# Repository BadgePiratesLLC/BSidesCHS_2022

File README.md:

# BSidesCHS_2022
BSides Charleston 2022

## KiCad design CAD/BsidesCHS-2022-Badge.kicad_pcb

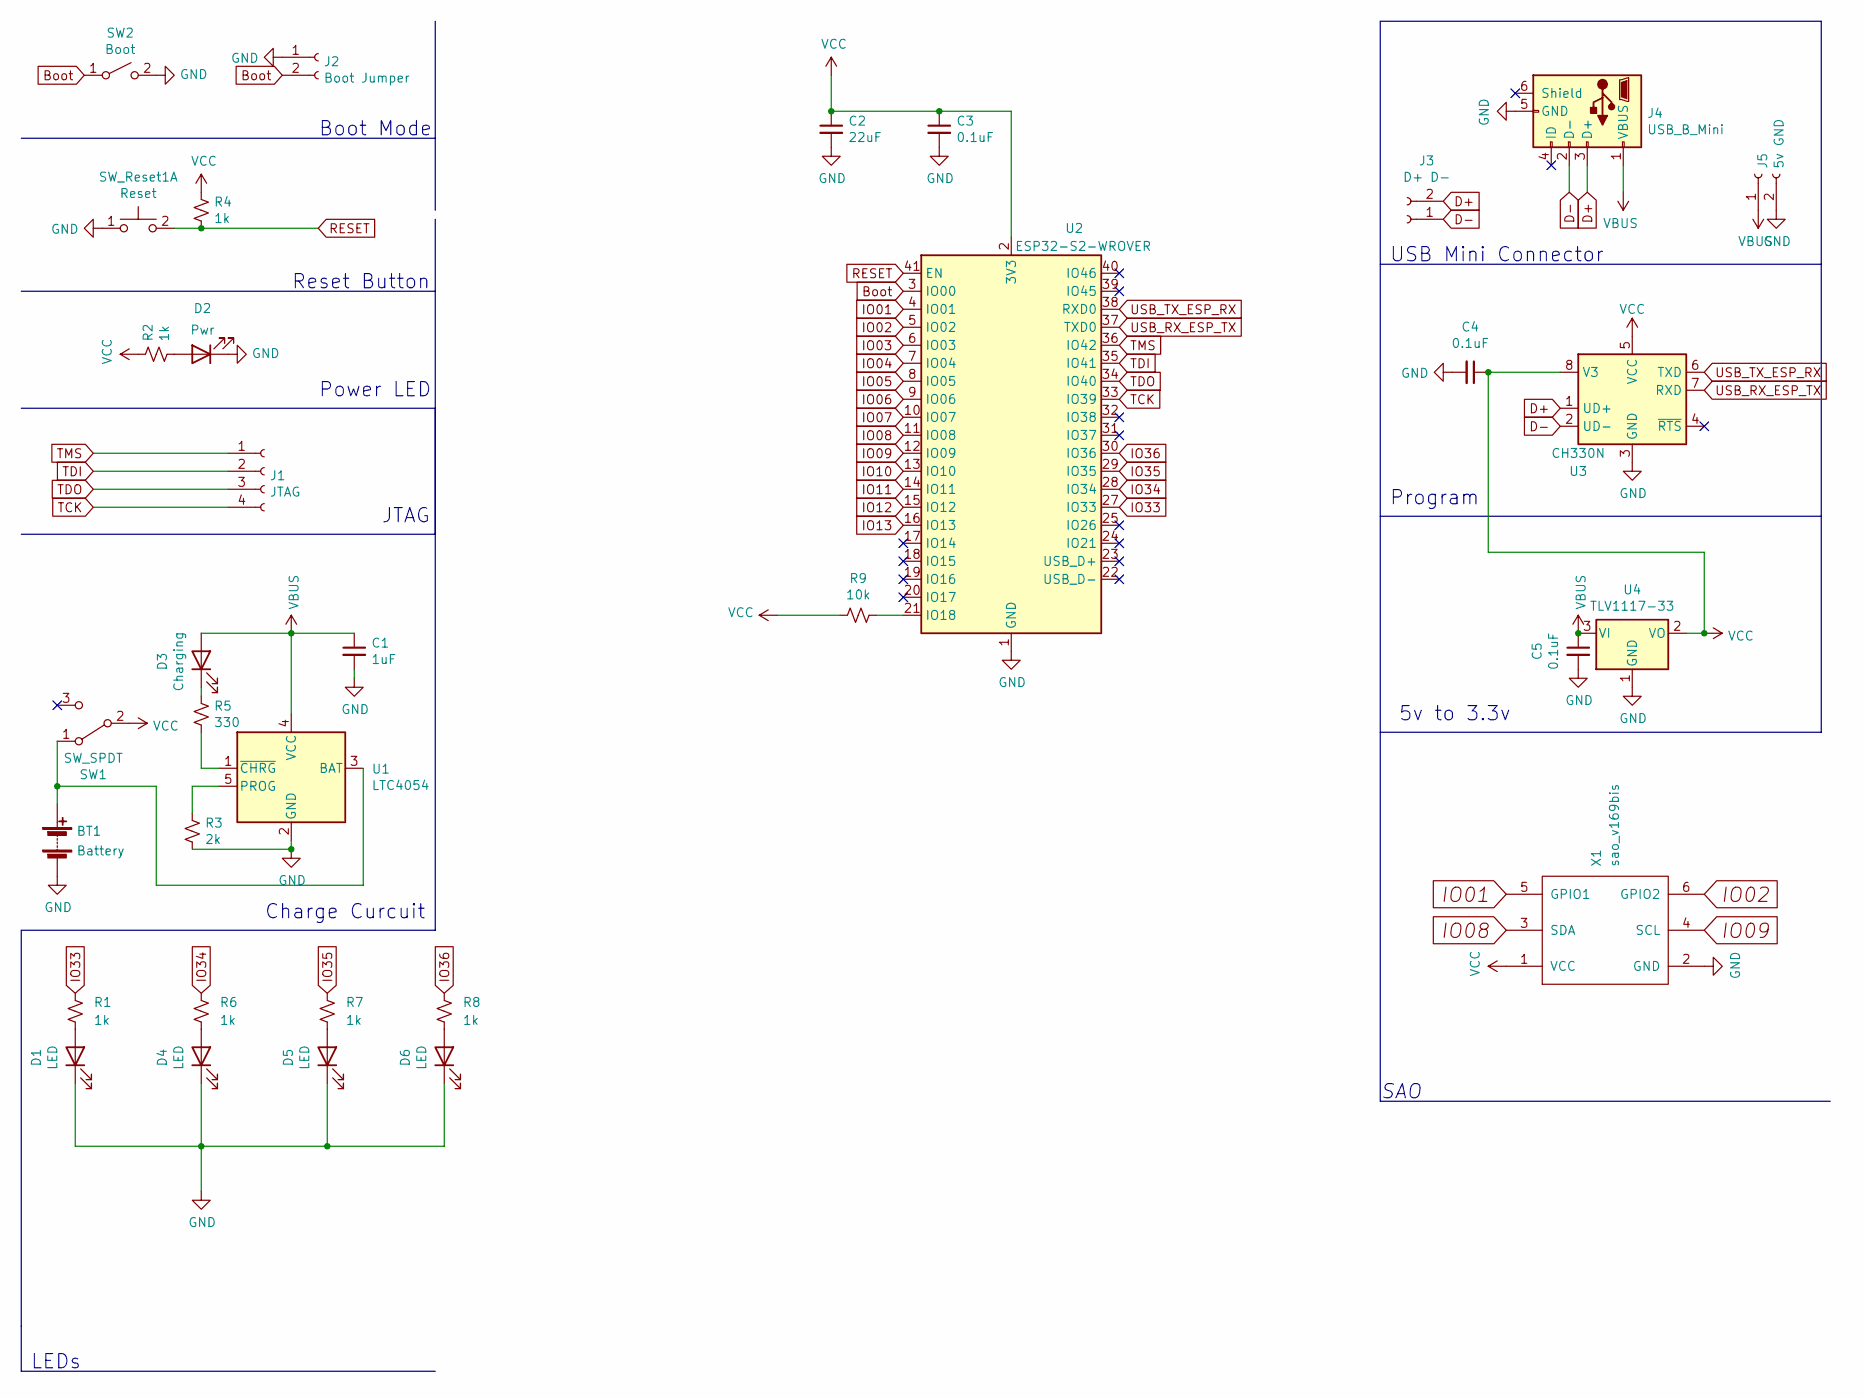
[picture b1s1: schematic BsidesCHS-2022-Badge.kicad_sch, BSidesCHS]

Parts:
BT1: Battery; Battery - 14500
C1: 1uF; C_0805_2012Metric
C2: 22uF; C_0805_2012Metric
C3, C4, C5: 0.1uF; C_0805_2012Metric
D1, D4, D5, D6: LED; LED_Osram_Lx_P47F_D2mm_ReverseMount_Proper_Mask Only
D2: Pwr; R_1206_3216Metric
D3: Charging; LED_1206_3216Metric
J1: JTAG; PinHeader_1x04_P2.54mm_Vertical
J2: Boot Jumper; TestPoint_Pad_D2.0mm x2
J3: D+ D-; PinHeader_1x02_P2.54mm_Vertical
J4: USB_B_Mini; USB_Micro-B_Wuerth
J5: 5v GND; PinHeader_1x02_P2.54mm_Vertical
R1, R2, R4, R6, R7, R8: 1k; R_1206_3216Metric
R3: 2k; R_1206_3216Metric
R5: 330; R_1206_3216Metric
R9: 10k; R_1206_3216Metric
SW1: SW_SPDT; SW_SPDT_PCM12
SW2: Boot; Switch_Tactile_SMD_B3U-1000P-BPVersion
SW_Reset1: Reset; Switch_Tactile_SMD_B3U-1000P-BPVersion
U1: LTC4054
U2: ESP32-S2-WROVER; ESP32-S2-WROOM
U3: CH330N; SOIC-8-1EP_W3.9mm
U4: TLV1117-33; SOT-223
X1: sao_v169bis; Badgelife-SAOv169-SAO_Side_B.SLK

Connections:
Boot: J2.2 (Pin_1), SW2.1 (A), U2.3 (IO00)
D+: J3.2, J4.3 (D+), U3.1 (UD+)
D-: J3.1, J4.2 (D-), U3.2 (UD-)
GND: BT1.2 (-), C1.2, C2.2, C3.2, C4.2, C5.2, D1.1 (K), D2.1 (K), D4.1 (K), D5.1 (K), D6.1 (K), J2.1, J4.5 (GND), J5.2, R3.2, SW2.2 (B), SW_Reset1.1 (C), U1.2 (GND), U2.1 (GND), U2.26 (GND), U2.42 (GND), U2.43 (GND), U3.3 (GND), U4.1 (GND), X1.2 (GND)
IO01: U2.4 (IO01), X1.5 (GPIO1)
IO02: U2.5 (IO02), X1.6 (GPIO2)
IO03: U2.6 (IO03)
IO04: U2.7 (IO04)
IO05: U2.8 (IO05)
IO06: U2.9 (IO06)
IO07: U2.10 (IO07)
IO08: U2.11 (IO08), X1.3 (SDA)
IO09: U2.12 (IO09), X1.4 (SCL)
IO10: U2.13 (IO10)
IO11: U2.14 (IO11)
IO12: U2.15 (IO12)
IO13: U2.16 (IO13)
IO33: R1.1, U2.27 (IO33)
IO34: R6.1, U2.28 (IO34)
IO35: R7.1, U2.29 (IO35)
IO36: R8.1, U2.30 (IO36)
unnamed: BT1.1 (+), SW1.1 (A), U1.3 (BAT)
unnamed: D1.2 (A), R1.2
unnamed: D2.2 (A), R2.2
unnamed: D3.1 (K), R5.1
unnamed: D4.2 (A), R6.2
unnamed: D5.2 (A), R7.2
unnamed: D6.2 (A), R8.2
unnamed: R3.1, U1.5 (PROG)
unnamed: R5.2, U1.1 (~CHRG)
unnamed: R9.1, U2.21 (IO18)
RESET: R4.2, SW_Reset1.2 (D), U2.41 (EN)
TCK: J1.4, U2.33 (IO39)
TDI: J1.2, U2.35 (IO41)
TDO: J1.3, U2.34 (IO40)
TMS: J1.1, U2.36 (IO42)
USB_RX_ESP_TX: U2.37 (TXD0), U3.7 (RXD)
USB_TX_ESP_RX: U2.38 (RXD0), U3.6 (TXD)
VBUS: C1.1, C5.1, D3.2 (A), J4.1 (VBUS), J5.1, U1.4 (VCC), U4.3 (VI)
VCC: C2.1, C3.1, C4.1, R2.1, R4.1, R9.2, SW1.2 (B), U2.2 (3V3), U3.5 (VCC), U3.8 (V3), U4.2 (VO), X1.1 (VCC)

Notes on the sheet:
SAO
Charge Curcuit
Power LED
USB Mini Connector
JTAG
5v to 3.3v
Program
Boot Mode
Reset Button
LEDs

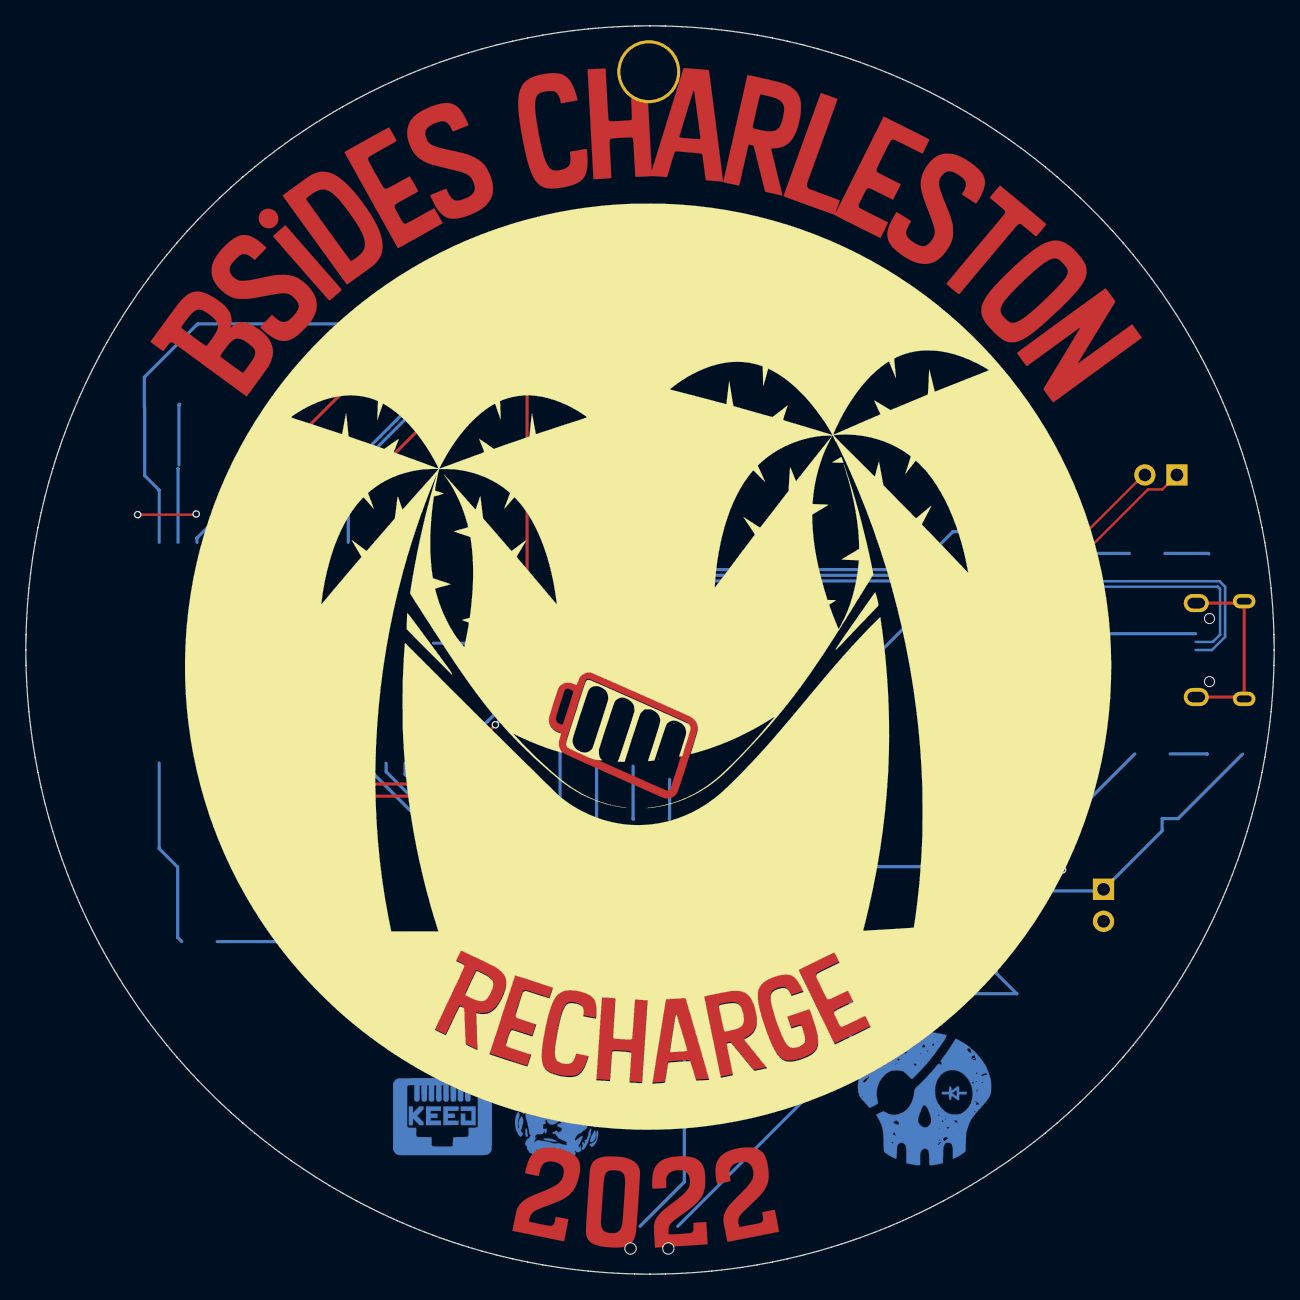
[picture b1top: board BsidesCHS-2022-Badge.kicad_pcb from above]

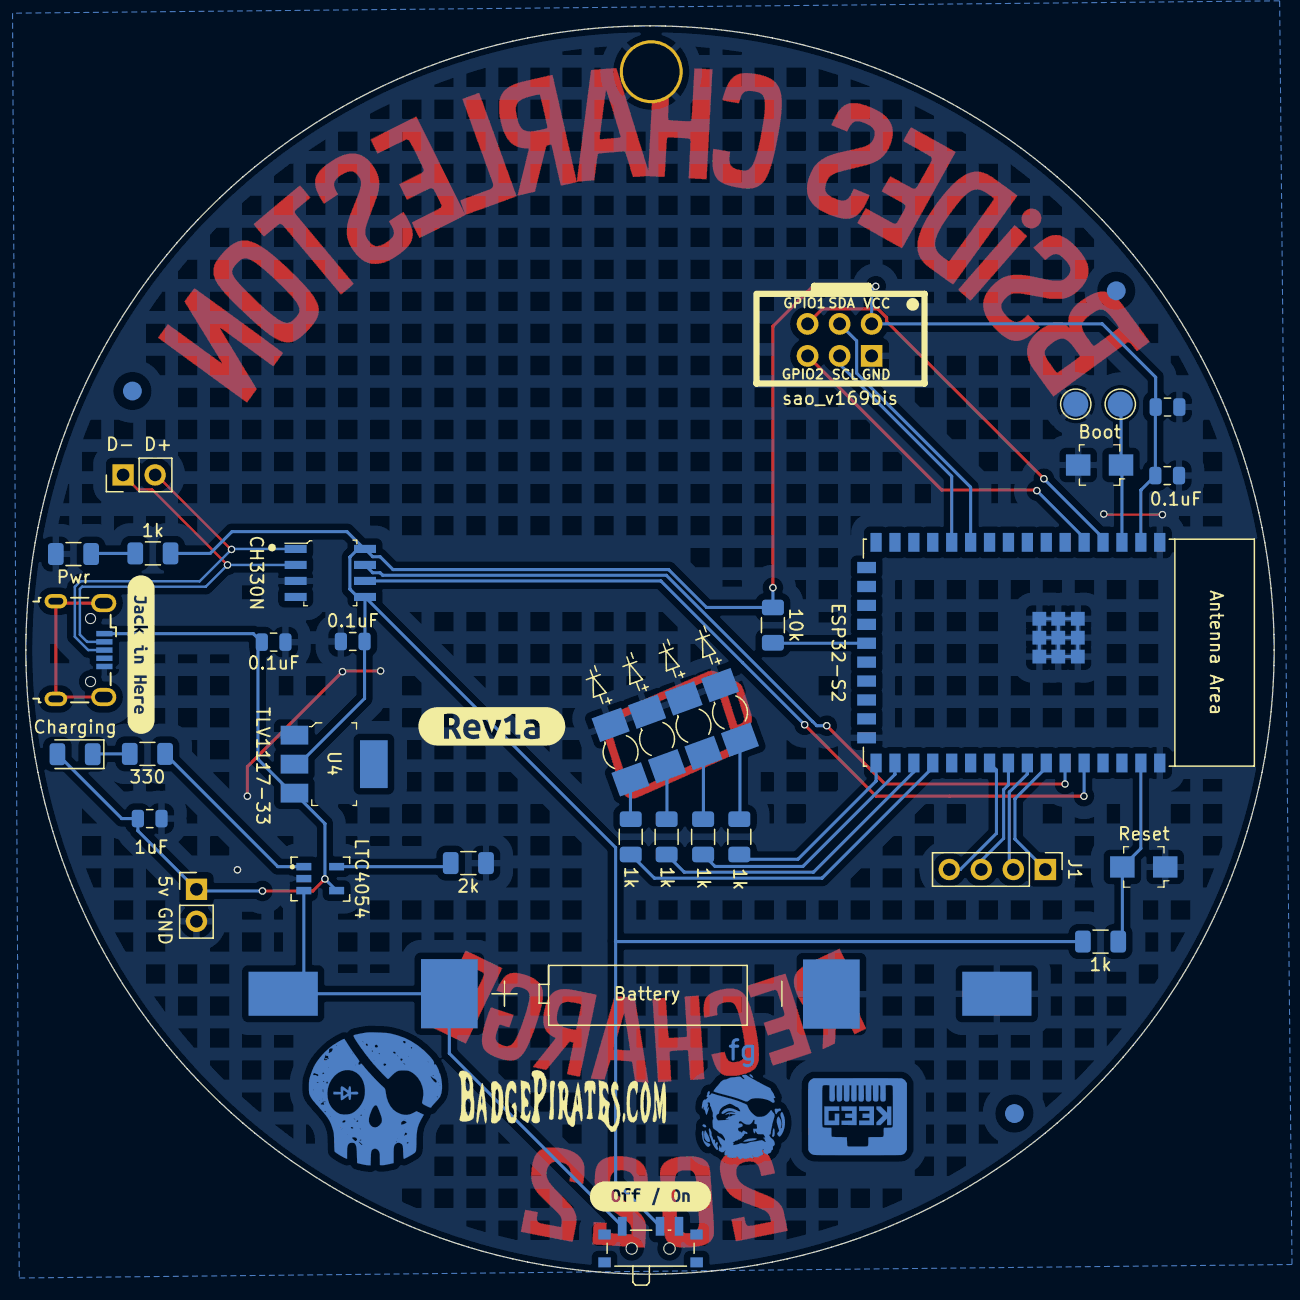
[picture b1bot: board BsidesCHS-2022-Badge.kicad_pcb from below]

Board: 2 copper layers, 99.0 x 99.0 mm, 37 parts (32 on the bottom side), 31 nets.

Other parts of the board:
kibuzzard-633CCB9B: G***; kibuzzard-633CCB9B
kibuzzard-6328D1ED: G***; kibuzzard-6328D1ED
kibuzzard-6328D231: G***; kibuzzard-6328D231
